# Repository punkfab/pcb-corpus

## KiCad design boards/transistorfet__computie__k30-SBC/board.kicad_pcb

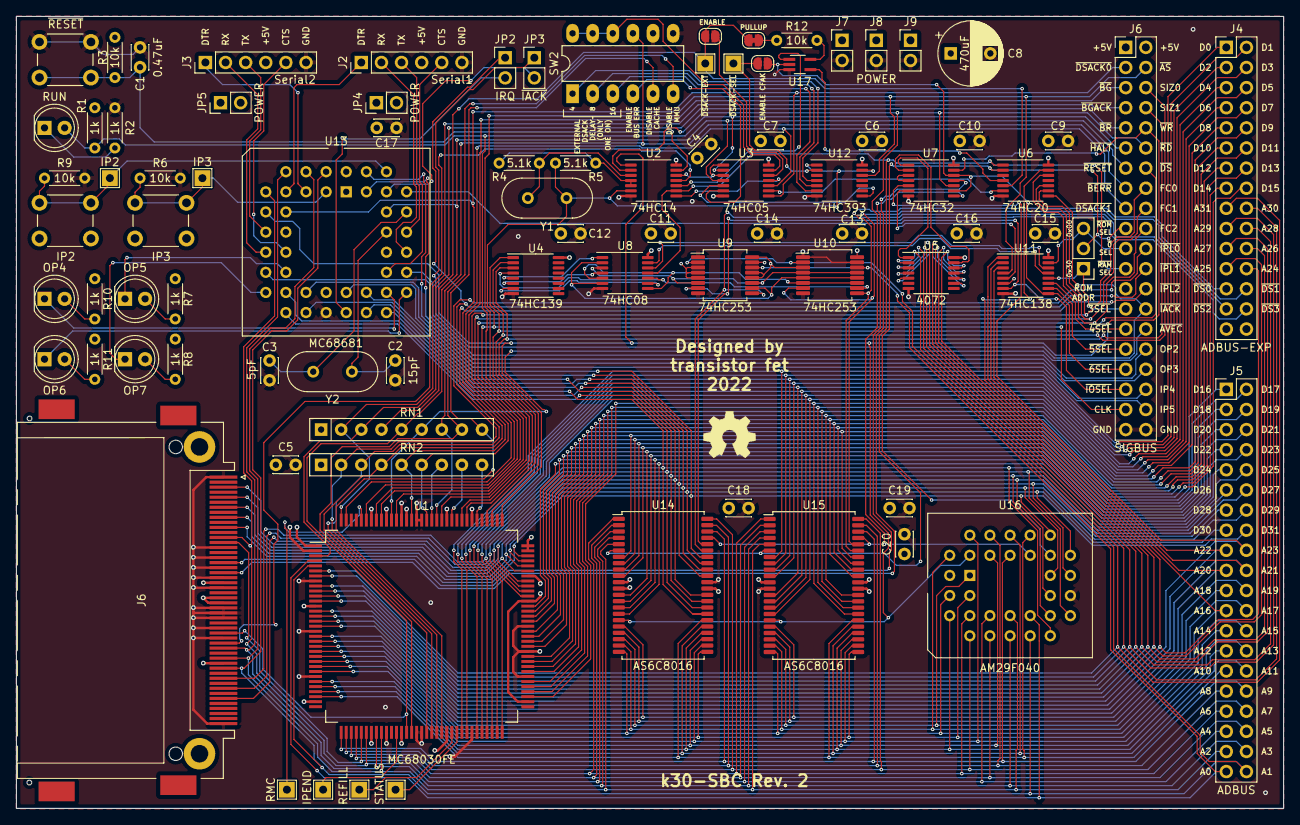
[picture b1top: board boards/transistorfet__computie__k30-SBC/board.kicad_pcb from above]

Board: 4 copper layers, 160.0 x 100.0 mm, 87 parts (0 on the bottom side), 173 nets.

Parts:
C1: 0.47uF; C_Disc_D3.0mm_W2.0mm_P2.50mm
C2: 15pF; C_Disc_D3.0mm_W2.0mm_P2.50mm
C3: 5pF; C_Disc_D3.0mm_W2.0mm_P2.50mm
C4, C5, C6, C7, C9, C10, C11, C12, C13, C14, C15, C16, C17, C18, C19, C20: 0.1uF; C_Disc_D3.0mm_W2.0mm_P2.50mm
C8: 470uF; CP_Radial_D8.0mm_P5.00mm
D1: RUN; LED_D5.0mm
D2: OP5; LED_D5.0mm
D3: OP7; LED_D5.0mm
D4: OP4; LED_D5.0mm
D5: OP6; LED_D5.0mm
J1: CompactFlash; CF-Card_3M_N7E50-Q516RB-40
J2: Serial1; PinHeader_1x06_P2.54mm_Vertical
J3: Serial2; PinHeader_1x06_P2.54mm_Vertical
J4: ADBUS-EXP; PinHeader_2x15_P2.54mm_Vertical
J5: ADBUS; PinHeader_2x20_P2.54mm_Vertical
J6: SIGBUS; PinHeader_2x20_P2.54mm_Vertical
J7, J8, J9: POWER; PinHeader_1x02_P2.54mm_Vertical
JP1: ROMJMP; PinHeader_1x03_P2.54mm_Vertical
JP2: IRQ; PinHeader_1x02_P2.54mm_Vertical
JP3: ~{IACK}; PinHeader_1x02_P2.54mm_Vertical
JP4, JP5: POWER; PinHeader_1x02_P2.54mm_Vertical
JP6: ENABLE; SolderJumper-2_P1.3mm_Open_RoundedPad1.0x1.5mm
JP7: PULLUP; SolderJumper-2_P1.3mm_Bridged_RoundedPad1.0x1.5mm
JP8: ENABLE CFAK; SolderJumper-2_P1.3mm_Open_RoundedPad1.0x1.5mm
R1, R2, R7, R8, R10, R11: 1k; R_Axial_DIN0204_L3.6mm_D1.6mm_P5.08mm_Horizontal
R3, R6, R9, R12: 10k; R_Axial_DIN0204_L3.6mm_D1.6mm_P5.08mm_Horizontal
R4, R5: 5.1k; R_Axial_DIN0204_L3.6mm_D1.6mm_P5.08mm_Horizontal
RN1, RN2: 10k; R_Array_SIP9
SW1: ~{RESET}; SW_PUSH_6mm
SW2: SW_DIP_x06; DIP-12_W7.62mm_LongPads
SW3: IP2; SW_PUSH_6mm
SW4: IP3; SW_PUSH_6mm
TP1: IPEND; TestPoint_THTPad_2.0x2.0mm_Drill1.0mm
TP2: REFILL; TestPoint_THTPad_2.0x2.0mm_Drill1.0mm
TP3: STATUS; TestPoint_THTPad_2.0x2.0mm_Drill1.0mm
TP4: ~{DSACK-EXT}; TestPoint_THTPad_2.0x2.0mm_Drill1.0mm
TP5: IP3; TestPoint_THTPad_2.0x2.0mm_Drill1.0mm
TP6: IP2; TestPoint_THTPad_2.0x2.0mm_Drill1.0mm
TP7: RMC; TestPoint_THTPad_2.0x2.0mm_Drill1.0mm
TP8: ~{DSACK-SEL}; TestPoint_THTPad_2.0x2.0mm_Drill1.0mm
U1: MC68030FE; PQFP-132_24x24mm_P0.635mm
U2: 74HC14; TSSOP-14_4.4x5mm_P0.65mm
U3: 74HC05; TSSOP-14_4.4x5mm_P0.65mm
U4: 74HC139; TSSOP-16_4.4x5mm_P0.65mm
U5: 4072; TSSOP-14_4.4x5mm_P0.65mm
U6: 74HC20; TSSOP-14_4.4x5mm_P0.65mm
U7: 74HC32; TSSOP-14_4.4x5mm_P0.65mm
U8: 74HC08; TSSOP-14_4.4x5mm_P0.65mm
U9, U10: 74HC253; SSOP-16_5.3x6.2mm_P0.65mm
U11: 74HC138; TSSOP-16_4.4x5mm_P0.65mm
U12: 74HC393; TSSOP-14_4.4x5mm_P0.65mm
U13: MC68681; PLCC-44_THT-Socket
U14, U15: AS6C8016; TSOP-II-44_10.16x18.41mm_P0.8mm
U16: AM29F040; PLCC-32_THT-Socket
U17: 74LVC1G32; SOT-353_SC-70-5_Handsoldering
Y1, Y2: Crystal; Crystal_HC49-4H_Vertical

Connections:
+5V: C4.1, C5.1, C6.1, C7.1, C8.1, C9.1, C10.1, C11.1, C12.1, C13.1, C14.1, C15.1, C16.1, C17.1, C18.1, C19.1, C20.1, J1.13, J1.36, J1.38, J1.44, J6.1, J6.2, J7.1, J8.1, J9.1, JP4.1 (A), JP5.1 (A), R1.2, R3.1, R7.2, R8.2, R10.2, R11.2, R12.1, RN1.1 (common), RN2.1 (common), SW3.2, SW4.2, U1.1 (VCC), U1.13 (VCC), U1.32 (VCC), U1.46 (VCC), U1.55 (VCC), U1.68 (VCC), U1.88 (VCC), U1.98 (VCC), U1.99 (VCC), U1.111 (VCC), U1.119 (VCC), U1.123 (VCC), U2.14 (VCC), U3.14 (VCC), U4.16 (VCC), U5.14 (VDD), U6.14 (VCC), U7.14 (VCC), U8.14 (VCC), U9.3 (I3a), U9.4 (I2a), U9.5 (I1a), U9.12 (I2b), U9.13 (I3b), U9.16 (VCC), U10.3 (I3a), U10.16 (VCC), U11.6 (E3), U11.16 (VCC), U12.14 (VCC), U13.44 (VCC), U14.11 (VCC), U14.33 (VCC), U15.11 (VCC), U15.33 (VCC), U16.32 (VCC), U17.5 (VCC)
A0: J5.39, U1.4 (A0), U9.14 (A0), U10.14 (A0), U16.12 (A0)
A1: J1.20, J5.40, U1.5 (A1), U9.2 (A1), U10.2 (A1), U13.2 (RS1), U16.11 (A1)
A2: J1.19, J5.37, U1.42 (A2), U13.4 (RS2), U14.5 (A0), U15.5 (A0), U16.10 (A2)
A3: J1.18, J5.38, U1.41 (A3), U13.6 (RS3), U14.4 (A1), U15.4 (A1), U16.9 (A3)
A4: J1.7, J5.35, U1.39 (A4), U13.7 (RS4), U14.3 (A2), U15.3 (A2), U16.8 (A4)
A5: J1.32, J5.36, U1.38 (A5), U14.2 (A3), U15.2 (A3), U16.7 (A5)
A6: J5.33, U1.37 (A6), U14.1 (A4), U15.1 (A4), U16.6 (A6)
A7: J5.34, U1.36 (A7), U14.44 (A5), U15.44 (A5), U16.5 (A7)
A8: J5.31, U1.35 (A8), U14.43 (A6), U15.43 (A6), U16.27 (A8)
A9: J5.32, U1.34 (A9), U14.42 (A7), U15.42 (A7), U16.26 (A9)
A10: J5.29, U1.31 (A10), U14.28 (A8), U15.28 (A8), U16.23 (A10)
A11: J5.30, U1.30 (A11), U14.27 (A9), U15.27 (A9), U16.25 (A11)
A12: J5.27, U1.29 (A12), U14.26 (A10), U15.26 (A10), U16.4 (A12)
A13: J5.28, U1.28 (A13), U14.25 (A11), U15.25 (A11), U16.28 (A13)
A14: J5.25, U1.26 (A14), U14.24 (A12), U15.24 (A12), U16.29 (A14)
A15: J5.26, U1.25 (A15), U14.23 (A13), U15.23 (A13), U16.3 (A15)
A16: J5.23, U1.24 (A16), U6.13, U14.22 (A14), U15.22 (A14), U16.2 (A16)
A17: J5.24, U1.23 (A17), U14.21 (A15), U15.21 (A15), U16.30 (A17)
A18: J5.21, U1.22 (A18), U14.20 (A16), U15.20 (A16), U16.1 (A18)
A19: J5.22, U1.21 (A19), U14.19 (A17), U15.19 (A17)
A20: J5.19, U1.20 (A20), U11.1 (A0), U14.18 (A18), U15.18 (A18)
A21: J5.20, U1.19 (A21), U11.2 (A1)
A22: J5.17, U1.17 (A22), U11.3 (A2)
A23: J5.18, U1.16 (A23), U7.5
A24: J4.24, U1.15 (A24), U5.12
A25: J4.23, U1.14 (A25), U5.11
A26: J4.22, U1.12 (A26), U5.10
A27: J4.21, U1.11 (A27), U5.9
A28: J4.20, U1.10 (A28), U5.5
A29: J4.19, U1.9 (A29), U5.4
A30: J4.18, U1.7 (A30), U5.3
A31: J4.17, U1.6 (A31), U5.2
ATA-READY: J1.42, U2.11
CLK: J6.37, R5.1, U1.121 (CLK), U2.6, U12.1 (CP), U12.13 (CP), Y1.2
D0: J4.1, U1.58 (D0), U15.7 (Q0)
D1: J4.2, U1.59 (D1), U15.8 (Q1)
D2: J4.3, U1.61 (D2), U15.9 (Q2)
D3: J4.4, U1.62 (D3), U15.10 (Q3)
D4: J4.5, U1.63 (D4), U15.13 (Q4)
D5: J4.6, U1.64 (D5), U15.14 (Q5)
D6: J4.7, U1.65 (D6), U15.15 (Q6)
D7: J4.8, U1.66 (D7), U15.16 (Q7)
D8: J4.9, U1.69 (D8), U15.29 (Q8)
D9: J4.10, U1.70 (D9), U15.30 (Q9)
D10: J4.11, U1.71 (D10), U15.31 (Q10)
D11: J4.12, U1.72 (D11), U15.32 (Q11)
D12: J4.13, U1.74 (D12), U15.35 (Q12)
D13: J4.14, U1.75 (D13), U15.36 (Q13)
D14: J4.15, U1.76 (D14), U15.37 (Q14)
D15: J4.16, U1.77 (D15), U15.38 (Q15)
D16: J5.1, U1.79 (D16), U14.7 (Q0)
D17: J5.2, U1.80 (D17), U14.8 (Q1)
D18: J5.3, U1.81 (D18), U14.9 (Q2)
D19: J5.4, U1.82 (D19), U14.10 (Q3)
D20: J5.5, U1.84 (D20), U14.13 (Q4)
D21: J5.6, U1.85 (D21), U14.14 (Q5)
D22: J5.7, U1.86 (D22), U14.15 (Q6)
D23: J5.8, U1.87 (D23), U14.16 (Q7)
D24: J1.21, J5.9, U1.89 (D24), U13.28 (D0), U14.29 (Q8), U16.13 (Q0)
D25: J1.22, J5.10, U1.90 (D25), U13.18 (D1), U14.30 (Q9), U16.14 (Q1)
D26: J1.23, J5.11, U1.91 (D26), U13.27 (D2), U14.31 (Q10), U16.15 (Q2)
D27: J1.2, J5.12, U1.92 (D27), U13.19 (D3), U14.32 (Q11), U16.17 (Q3)
D28: J1.3, J5.13, U1.94 (D28), U13.26 (D4), U14.35 (Q12), U16.18 (Q4)
D29: J1.4, J5.14, U1.95 (D29), U13.20 (D5), U14.36 (Q13), U16.19 (Q5)
D30: J1.5, J5.15, U1.96 (D30), U13.25 (D6), U14.37 (Q14), U16.20 (Q6)
D31: J1.6, J5.16, U1.97 (D31), U13.21 (D7), U14.38 (Q15), U16.21 (Q7)
FC0: J6.16, U1.127 (FC0), U6.9
FC1: J6.18, U1.125 (FC1), U6.10
FC2: J6.20, U1.124 (FC2), U6.12
GND: C1.2, C2.1, C3.1, C4.2, C5.2, C6.2, C7.2, C8.2, C9.2, C10.2, C11.2, C12.2, C13.2, C14.2, C15.2, C16.2, C17.2, C18.2, C19.2, C20.2, J1.1, J1.8, J1.9, J1.10, J1.11, J1.12, J1.14, J1.15, J1.16, J1.17, J1.39, J1.50, J2.6, J3.6, J6.39, J6.40, J7.2, J8.2, J9.2, R2.1, R6.2, R9.2, SW1.1, SW2.7, SW2.8, U1.2 (GND), U1.8 (GND), U1.18 (GND), U1.27 (GND), U1.40 (GND), U1.43 (GND), U1.49 (GND), U1.50 (GND), U1.60 (GND), U1.73 (GND), U1.78 (GND), U1.83 (GND), U1.93 (GND), U1.106 (GND), U1.116 (GND), U1.117 (GND), U1.120 (GND), U1.126 (GND), U2.7 (GND), U3.7 (GND), U4.8 (GND), U5.7 (VSS), U6.7 (GND), U7.7 (GND), U8.7 (GND), U9.1 (OEa), U9.8 (GND), U9.15 (OEb), U10.1 (OEa), U10.8 (GND), U10.15 (OEb), U11.8 (GND), U12.7 (GND), U13.22 (GND), U14.12 (VSS), U14.34 (VSS), U15.12 (VSS), U15.34 (VSS), U16.16 (GND), U17.3 (GND)
IP4: J6.36, U13.43 (IP4)
IP5: J6.38, U13.42 (IP5)
unnamed: C1.1, R3.2, SW1.2, U2.13
unnamed: C2.2, U13.36 (X1/CLK), Y2.2
unnamed: C3.2, U13.37 (X2), Y2.1
unnamed: D1.1 (K), R2.2
unnamed: D2.1 (K), U13.16 (OP5)
unnamed: D2.2 (A), R7.1
unnamed: D3.1 (K), U13.17 (OP7)
unnamed: D3.2 (A), R8.1
unnamed: D4.1 (K), U13.30 (OP4)
unnamed: D4.2 (A), R10.1
unnamed: D5.1 (K), U13.29 (OP6)
unnamed: D5.2 (A), R11.1
unnamed: J2.1, U13.8 (IP0)
unnamed: J2.2, U13.33 (TXDA)
unnamed: J2.3, U13.35 (RXDA)
unnamed: J2.4, JP4.2 (B)
unnamed: J2.5, U13.32 (OP0)
unnamed: J3.1, U13.5 (IP1)
unnamed: J3.2, U13.13 (TXDB)
unnamed: J3.3, U13.11 (RXDB)
unnamed: J3.4, JP5.2 (B)
unnamed: J3.5, U13.14 (OP1)
unnamed: JP6.1 (A), U3.12
unnamed: JP7.2 (B), R12.2
unnamed: R4.1, R5.2, U2.4, U2.5
unnamed: R4.2, U2.3, Y1.1
unnamed: R6.1, SW4.1, TP5.1, U13.3 (IP3)
unnamed: R9.1, SW3.1, TP6.1, U13.40 (IP2)
unnamed: RN2.7 (R6), U1.114 (STERM)
unnamed: RN2.8 (R7), U1.110 (CBACK)
unnamed: RN2.9 (R8), U1.105 (CIIN)
unnamed: SW2.1, U12.4 (Q1)
unnamed: SW2.2, U12.5 (Q2)
unnamed: SW2.3, U12.6 (Q3)
unnamed: SW2.4, U3.6
unnamed: SW2.10, SW2.11, SW2.12, U3.13
unnamed: TP1.1, U1.45 (IPEND)
unnamed: TP2.1, U1.56 (REFILL)
unnamed: TP3.1, U1.57 (STATUS)
unnamed: TP7.1, U1.128 (RMC)
unnamed: JP8.2 (B), TP8.1, U12.2 (MR)
unnamed: U2.8, U3.11
unnamed: U2.12, U3.1, U3.3
unnamed: U3.9, U6.6
unnamed: U4.5 (O1), U8.1
unnamed: U4.6 (O2), U8.4
unnamed: U4.7 (O3), U8.9
unnamed: U5.1, U7.1
unnamed: U5.13, U7.2
unnamed: U7.3, U7.4
unnamed: U4.4 (O0), U8.10, U10.10 (I0b)
unnamed: U8.5, U8.8, U10.6 (I0a), U10.11 (I1b)
unnamed: U8.2, U8.6, U9.10 (I0b), U10.5 (I1a), U10.12 (I2b)
unnamed: U8.3, U9.6 (I0a), U9.11 (I1b), U10.4 (I2a), U10.13 (I3b)
unnamed: U7.6, U11.5 (E2)
unnamed: U8.13, U11.13 (O2)
unnamed: U8.12, U11.14 (O1)
unnamed: U3.5, U12.8 (Q3)
unnamed: U2.10, U17.1
OP2: J6.32, U13.31 (OP2)
OP3: J6.34, U13.15 (OP3)
SIZ0: J6.6, U1.103 (SIZ0), U4.2 (A0)
SIZ1: J6.8, U1.102 (SIZ1), U4.3 (A1)
~0SEL: J6.21, JP1.3 (B), U11.15 (O0)
~3SEL: J6.27, JP1.1 (A), U11.12 (O3)
~4SEL: J6.29, U11.11 (O4)
~5SEL: J6.31, U11.10 (O5)
~6SEL: J6.33, JP8.1 (A), U7.9, U7.12, U11.9 (O6), U17.2
~AS: J6.4, U1.108 (AS), U11.4 (E1), U12.12 (MR)
~ATA-DSACK: U6.4, U17.4
~AVEC: J6.30, RN1.6 (R5), U1.122 (AVEC)
~BERR: J6.15, RN1.7 (R6), SW2.9, U1.113 (BERR)
~BGACK: J6.7, RN1.2 (R1), U1.132 (BGACK)
~BG: J6.5, U1.131 (BG)
~BR: J6.9, RN1.3 (R2), U1.3 (BR)
~CDIS: RN1.9 (R8), SW2.5, U1.54 (CDIS)
~DS0: J4.25, U10.9 (Zb), U15.39 (~LB)
~DS1: J4.26, U10.7 (Za), U15.40 (~UB)
~DS2: J4.27, U9.9 (Zb), U14.39 (~LB)
~DS3: J4.28, U9.7 (Za), U14.40 (~UB)
~DSACK0: J6.3, RN2.5 (R4), U1.118 (DSACK0), U3.8, U13.10 (DTACK)
~DSACK1: J6.17, RN2.6 (R5), U1.115 (DSACK1), U3.10
~DSACK-EXT: JP6.2 (B), JP7.1 (A), RN1.4 (R3), TP4.1, U6.5
~DS: J6.14, U1.107 (DS), U4.1 (E)
~HALT: D1.2 (A), J6.11, R1.1, U1.112 (HALT), U3.2
~IACK: J6.28, JP3.1 (A), U6.8
~IORD: J1.34, U7.8
~IOSEL: J6.35, U11.7 (O7), U13.39 (CS)
~IOWR: J1.35, U7.11
~IPL0: J6.22, RN2.2 (R1), U1.53 (IPL0)
~IPL1: J6.24, JP2.1 (A), RN2.3 (R2), U1.52 (IPL1)
~IPL2: J6.26, RN2.4 (R3), U1.51 (IPL2)
~MMUDIS: RN1.8 (R7), SW2.6, U1.48 (MMUDIS)
~RAMSEL: J6.23, U2.9, U6.1, U8.11, U14.6 (~CE), U15.6 (~CE)
~RD: J6.12, U2.2, U7.10, U14.41 (~OE), U15.41 (~OE), U16.24 (~OE)
~RESET: J1.41, J6.13, RN1.5 (R4), U1.47 (RESET), U3.4, U13.38 (RESET)
~ROMSEL: J6.19, JP1.2 (C), U6.2, U16.22 (~CS)
~SIACK: JP3.2 (B), U13.41 (IACK)
~SIRQ: JP2.2 (B), U13.24 (IRQ)
~WR: J6.10, U1.100 (R/W), U2.1, U7.13, U13.9 (R/W), U14.17 (~WE), U15.17 (~WE), U16.31 (~WE)

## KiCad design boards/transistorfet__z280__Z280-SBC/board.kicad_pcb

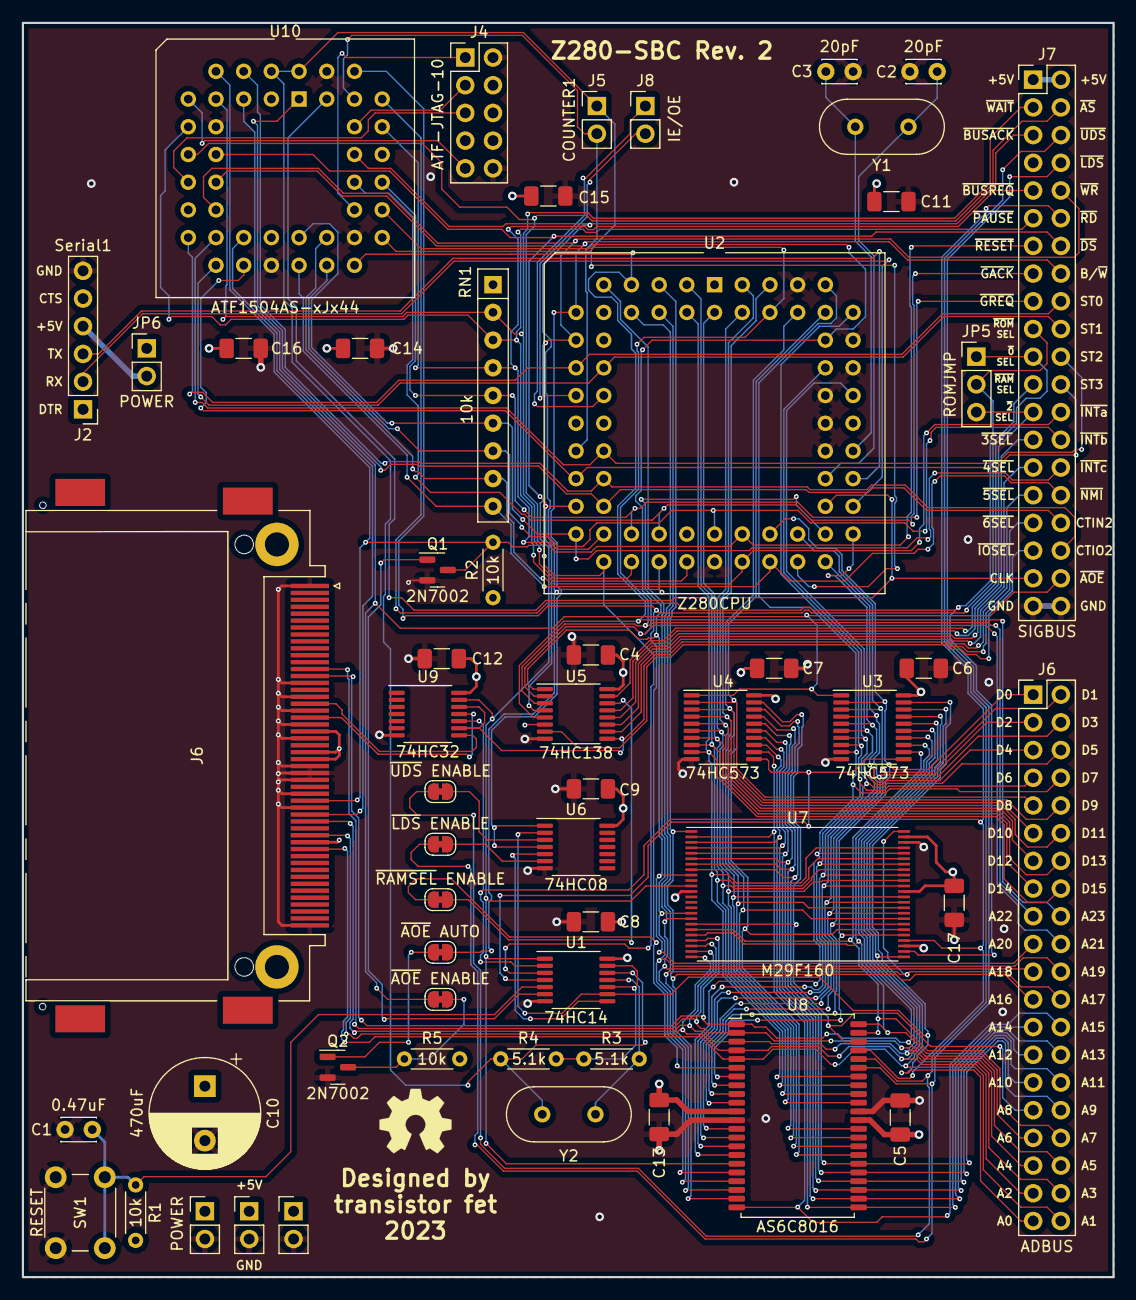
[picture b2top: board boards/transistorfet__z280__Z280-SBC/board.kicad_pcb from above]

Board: 4 copper layers, 100.0 x 115.0 mm, 55 parts (0 on the bottom side), 104 nets.

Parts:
C1: 0.47uF; C_Disc_D3.0mm_W2.0mm_P2.50mm
C2, C3: 20pF; C_Disc_D3.0mm_W2.0mm_P2.50mm
C4, C5, C6, C7, C8, C9, C11, C12, C13, C14, C15, C16, C17: 0.1uF; C_1206_3216Metric_Pad1.33x1.80mm_HandSolder
C10: 470uF; CP_Radial_D10.0mm_P5.00mm
J1: CompactFlash; CF-Card_3M_N7E50-Q516RB-40
J2: Serial1; PinHeader_1x06_P2.54mm_Vertical
J3, J9, J10: POWER; PinHeader_1x02_P2.54mm_Vertical
J4: ATF-JTAG-10; PinHeader_2x05_P2.54mm_Vertical
J5: COUNTER1; PinHeader_1x02_P2.54mm_Vertical
J6: ADBUS; PinHeader_2x20_P2.54mm_Vertical
J7: SIGBUS; PinHeader_2x20_P2.54mm_Vertical
J8: IE/OE; PinHeader_1x02_P2.54mm_Vertical
JP1: ~{AOE} ENABLE; SolderJumper-2_P1.3mm_Bridged_RoundedPad1.0x1.5mm
JP2: ~{UDS} ENABLE; SolderJumper-2_P1.3mm_Bridged_RoundedPad1.0x1.5mm
JP3: ~{LDS} ENABLE; SolderJumper-2_P1.3mm_Bridged_RoundedPad1.0x1.5mm
JP4: ~{RAMSEL} ENABLE; SolderJumper-2_P1.3mm_Bridged_RoundedPad1.0x1.5mm
JP5: ROMJMP; PinHeader_1x03_P2.54mm_Vertical
JP6: POWER; PinHeader_1x02_P2.54mm_Vertical
JP7: ~{AOE} AUTO; SolderJumper-2_P1.3mm_Bridged_RoundedPad1.0x1.5mm
Q1, Q2: 2N7002; SOT-23
R1, R2, R5: 10k; R_Axial_DIN0204_L3.6mm_D1.6mm_P5.08mm_Horizontal
R3, R4: 5.1k; R_Axial_DIN0204_L3.6mm_D1.6mm_P5.08mm_Horizontal
RN1: 10k; R_Array_SIP9
SW1: RESET; SW_PUSH_6mm
U1: 74HC14; TSSOP-14_4.4x5mm_P0.65mm
U2: Z280CPU; PLCC-68_THT-Socket
U3, U4: 74HC573; TSSOP-20_4.4x6.5mm_P0.65mm
U5: 74HC138; TSSOP-16_4.4x5mm_P0.65mm
U6: 74HC08; TSSOP-14_4.4x5mm_P0.65mm
U7: M29F160; TSOP-I-48_18.4x12mm_P0.5mm
U8: AS6C8016; TSOP-II-44_10.16x18.41mm_P0.8mm
U9: 74HC32; TSSOP-14_4.4x5mm_P0.65mm
U10: ATF1504AS-xJx44; PLCC-44_THT-Socket
Y1, Y2: Crystal; Crystal_HC49-4H_Vertical

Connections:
+5V: C4.1, C5.1, C6.1, C7.1, C8.1, C9.1, C10.1, C11.1, C12.1, C13.1, C14.1, C15.1, C16.1, C17.1, J1.13, J1.36, J1.38, J1.44, J3.1, J4.7 (VCC), J7.1, J7.2, J9.1, J10.1, JP6.1 (A), R1.1, R2.1, R5.1, RN1.1 (common), U1.14 (VCC), U2.18 (VCC), U2.19 (VCC), U3.20 (VCC), U4.20 (VCC), U5.6 (E3), U5.16 (VCC), U6.14 (VCC), U7.12 (~RST), U7.37 (VCC), U7.47 (~BYTE), U8.11 (VCC), U8.33 (VCC), U9.14 (VCC), U10.3 (VCC), U10.15 (VCC), U10.23 (VCC), U10.35 (VCC)
A0: J6.39, U1.9, U3.19 (Q0), U6.2
A1: J1.20, J6.40, U3.18 (Q1), U7.25 (A0), U8.5 (A0)
A2: J1.19, J6.37, U3.17 (Q2), U7.24 (A1), U8.4 (A1)
A3: J1.18, J6.38, U3.16 (Q3), U7.23 (A2), U8.3 (A2)
A4: J1.7, J6.35, U3.15 (Q4), U7.22 (A3), U8.2 (A3)
A5: J1.32, J6.36, U3.14 (Q5), U7.21 (A4), U8.1 (A4)
A6: J6.33, U3.13 (Q6), U7.20 (A5), U8.44 (A5)
A7: J6.34, U3.12 (Q7), U7.19 (A6), U8.43 (A6)
A8: J6.31, U4.19 (Q0), U7.18 (A7), U8.42 (A7)
A9: J6.32, U4.18 (Q1), U7.8 (A8), U8.28 (A8)
A10: J6.29, U4.17 (Q2), U7.7 (A9), U8.27 (A9)
A11: J6.30, U4.16 (Q3), U7.6 (A10), U8.26 (A10)
A12: J6.27, U4.15 (Q4), U7.5 (A11), U8.25 (A11)
A13: J6.28, U4.14 (Q5), U7.4 (A12), U8.24 (A12)
A14: J6.25, U4.13 (Q6), U7.3 (A13), U8.23 (A13)
A15: J6.26, U4.12 (Q7), U7.2 (A14), U8.22 (A14)
A16: J6.23, U2.5 (A16), U7.1 (A15), U8.21 (A15)
A17: J6.24, U2.6 (A17), U7.48 (A16), U8.20 (A16)
A18: J6.21, U2.8 (A18), U7.17 (A17), U8.19 (A17)
A19: J6.22, U2.9 (A19), U7.16 (A18), U8.18 (A18)
A20: J6.19, U2.45 (A20), U5.1 (A0), U7.9 (A19)
A21: J6.20, U2.59 (A21), U5.2 (A1), U10.31 (I/O)
A22: J6.17, U2.66 (A22), U5.3 (A2), U10.29 (I/O)
A23: J6.18, U2.7 (A23), U5.5 (E2), U10.28 (I/O)
ALE: U1.4, U3.11 (Load), U4.11 (Load)
ATA-READY: J1.42, U10.21 (I/O)
B/~W: J7.16, U2.10 (B/~W), U6.1, U6.4, U10.14 (I/O)
CLK: J7.37, U2.47 (CLK), U10.43 (I/GCLK1)
CTIN1: J5.1, R4.1, U1.12, U2.41 (CTIN1), U10.2 (I/OE2/GCLK2), U10.44 (I/OE1), Y2.2
CTIN2: J7.34, U2.25 (CTIN2), U10.1 (I/GCLR)
CTIO1: J5.2, U2.20 (CTIO1), U10.41 (I/O/GCLK3)
CTIO2: J7.36, U2.23 (CTIO2), U10.4 (I/O)
D0: J6.1, U2.40 (AD0), U3.2 (D0), U7.29 (Q0), U8.7 (Q0)
D1: J6.2, U2.42 (AD1), U3.3 (D1), U7.31 (Q1), U8.8 (Q1)
D2: J6.3, U2.43 (AD2), U3.4 (D2), U7.33 (Q2), U8.9 (Q2)
D3: J6.4, U2.44 (AD3), U3.5 (D3), U7.35 (Q3), U8.10 (Q3)
D4: J6.5, U2.54 (AD4), U3.6 (D4), U7.38 (Q4), U8.13 (Q4)
D5: J6.6, U2.57 (AD5), U3.7 (D5), U7.40 (Q5), U8.14 (Q5)
D6: J6.7, U2.60 (AD6), U3.8 (D6), U7.42 (Q6), U8.15 (Q6)
D7: J6.8, U2.61 (AD7), U3.9 (D7), U7.44 (Q7), U8.16 (Q7)
D8: J6.9, U2.62 (AD8), U4.2 (D0), U7.30 (Q8), U8.29 (Q8)
D9: J6.10, U2.64 (AD9), U4.3 (D1), U7.32 (Q9), U8.30 (Q9)
D10: J6.11, U2.65 (AD10), U4.4 (D2), U7.34 (Q10), U8.31 (Q10)
D11: J6.12, U2.67 (AD11), U4.5 (D3), U7.36 (Q11), U8.32 (Q11)
D12: J6.13, U2.68 (AD12), U4.6 (D4), U7.39 (Q12), U8.35 (Q12)
D13: J6.14, U2.2 (AD13), U4.7 (D5), U7.41 (Q13), U8.36 (Q13)
D14: J6.15, U2.3 (AD14), U4.8 (D6), U7.43 (Q14), U8.37 (Q14)
D15: J6.16, U2.4 (AD15), U4.9 (D7), U7.45 (Q15), U8.38 (Q15)
GND: C1.2, C2.1, C3.1, C4.2, C5.2, C6.2, C7.2, C8.2, C9.2, C10.2, C11.2, C12.2, C13.2, C14.2, C15.2, C16.2, C17.2, J1.1, J1.8, J1.9, J1.10, J1.11, J1.12, J1.14, J1.15, J1.16, J1.17, J1.39, J1.50, J2.6, J3.2, J4.2 (GND), J4.10 (GND), J7.39, J7.40, J9.2, J10.2, Q1.2 (S), Q2.2 (S), SW1.1, U1.7 (GND), U2.1 (GND), U2.35 (GND), U2.51 (GND), U2.53 (GND), U2.55 (~RDY0), U2.56 (~RDY1), U2.58 (~RDY3), U2.63 (~RDY2), U3.10 (GND), U4.10 (GND), U5.8 (GND), U6.7 (GND), U7.27 (GND), U7.46 (GND), U8.12 (VSS), U8.34 (VSS), U9.7 (GND), U10.10 (GND), U10.22 (GND), U10.30 (GND), U10.42 (GND)
unnamed: C1.1, R1.2, SW1.2, U1.5
unnamed: C2.2, U2.49 (XTALO), Y1.1
unnamed: C3.2, U2.50 (XTALI), Y1.2
unnamed: J2.4, JP6.2 (B)
unnamed: J4.1 (TCK), U10.32 (I/O/TCK)
unnamed: J4.3 (TDO), U10.38 (I/O/TDO)
unnamed: J4.5 (TMS), U10.13 (I/O/TMS)
unnamed: J4.9 (TDI), U10.7 (I/O/TDI)
unnamed: JP1.2 (B), Q2.3 (D), R5.2
unnamed: JP2.1 (A), U6.3
unnamed: JP3.1 (A), U6.6
unnamed: JP4.1 (A), U5.14 (O1)
unnamed: JP7.1 (A), Q2.1 (G)
unnamed: Q1.1 (G), U1.6
unnamed: R3.1, R4.2, U1.10, U1.13
unnamed: R3.2, U1.11, Y2.1
unnamed: U1.8, U6.5
RxD: J2.3, U2.48 (RxD)
R/~W: J7.10, U1.1, U2.12 (R/~W), U7.11 (~WE), U8.17 (~WE), U9.13, U10.16 (I/O)
ST0: J7.18, U2.14 (ST0), U10.17 (I/O)
ST1: J7.20, U2.15 (ST1), U10.18 (I/O)
ST2: J7.22, U2.21 (ST2), U10.19 (I/O)
ST3: J7.24, U2.22 (ST3), U10.20 (I/O)
TxD: J2.2, U2.46 (TxD)
~0SEL: J7.21, JP5.1 (A), U5.15 (O0)
~2SEL: J7.25, JP5.3 (B), U5.13 (O2)
~3SEL: J7.27, U5.12 (O3)
~4SEL: J7.29, U5.11 (O4)
~5SEL: J7.31, U5.10 (O5)
~6SEL: J7.33, U5.9 (O6), U9.9, U9.12
~AOE: J7.38, JP1.1 (A), U3.1 (OE), U4.1 (OE), U10.5 (I/O)
~AS: J7.4, U1.3, U2.27 (~AS), U10.11 (I/O/PD1)
~BUSACK: J7.5, JP7.2 (B), U2.31 (~BUSACK), U10.36 (I/O)
~BUSREQ: J7.9, RN1.4 (R3), U2.28 (~BUSREQ), U10.37 (I/O)
~DS: J7.14, U2.24 (~DS), U5.4 (E1), U10.12 (I/O)
~GACK: J7.15, U2.32 (CTIN0/~GACK), U10.34 (I/O)
~GREQ: J7.17, RN1.5 (R4), U2.30 (CTIO0/~GREQ), U10.33 (I/O)
~IE: J8.1, U2.17 (~IE)
~INTa: J7.26, RN1.8 (R7), U2.37 (~INTa/EOPa), U10.27 (I/O)
~INTb: J7.28, RN1.7 (R6), U2.36 (~INTb/EOPb), U10.26 (I/O)
~INTc: J7.30, RN1.6 (R5), U2.26 (~INTc), U10.25 (I/O/PD2)
~IORD: J1.34, U9.8
~IOSEL: J7.35, U5.7 (O7)
~IOWR: J1.35, U9.11
~LDS: J7.8, JP3.2 (B), U8.39 (~LB)
~NMI: J7.32, RN1.9 (R8), U2.39 (~NMI), U10.24 (I/O)
~OE: J8.2, U2.16 (~OE)
~PAUSE: J7.11, RN1.3 (R2), U2.33 (~PAUSE), U10.9 (I/O)
~RAMSEL: J7.23, JP4.2 (B), U8.6 (~CE), U10.40 (I/O)
~RD: J7.12, U1.2, U7.28 (~OE), U8.41 (~OE), U9.10
~RESET: J1.41, J7.13, Q1.3 (D), R2.2, U2.38 (~RESET), U10.6 (I/O)
~ROMSEL: J7.19, JP5.2 (C), U7.26 (~CS), U10.39 (I/O)
~UDS: J7.6, JP2.2 (B), U8.40 (~UB)
~WAIT: J7.3, RN1.2 (R1), U2.29 (~WAIT), U10.8 (I/O)

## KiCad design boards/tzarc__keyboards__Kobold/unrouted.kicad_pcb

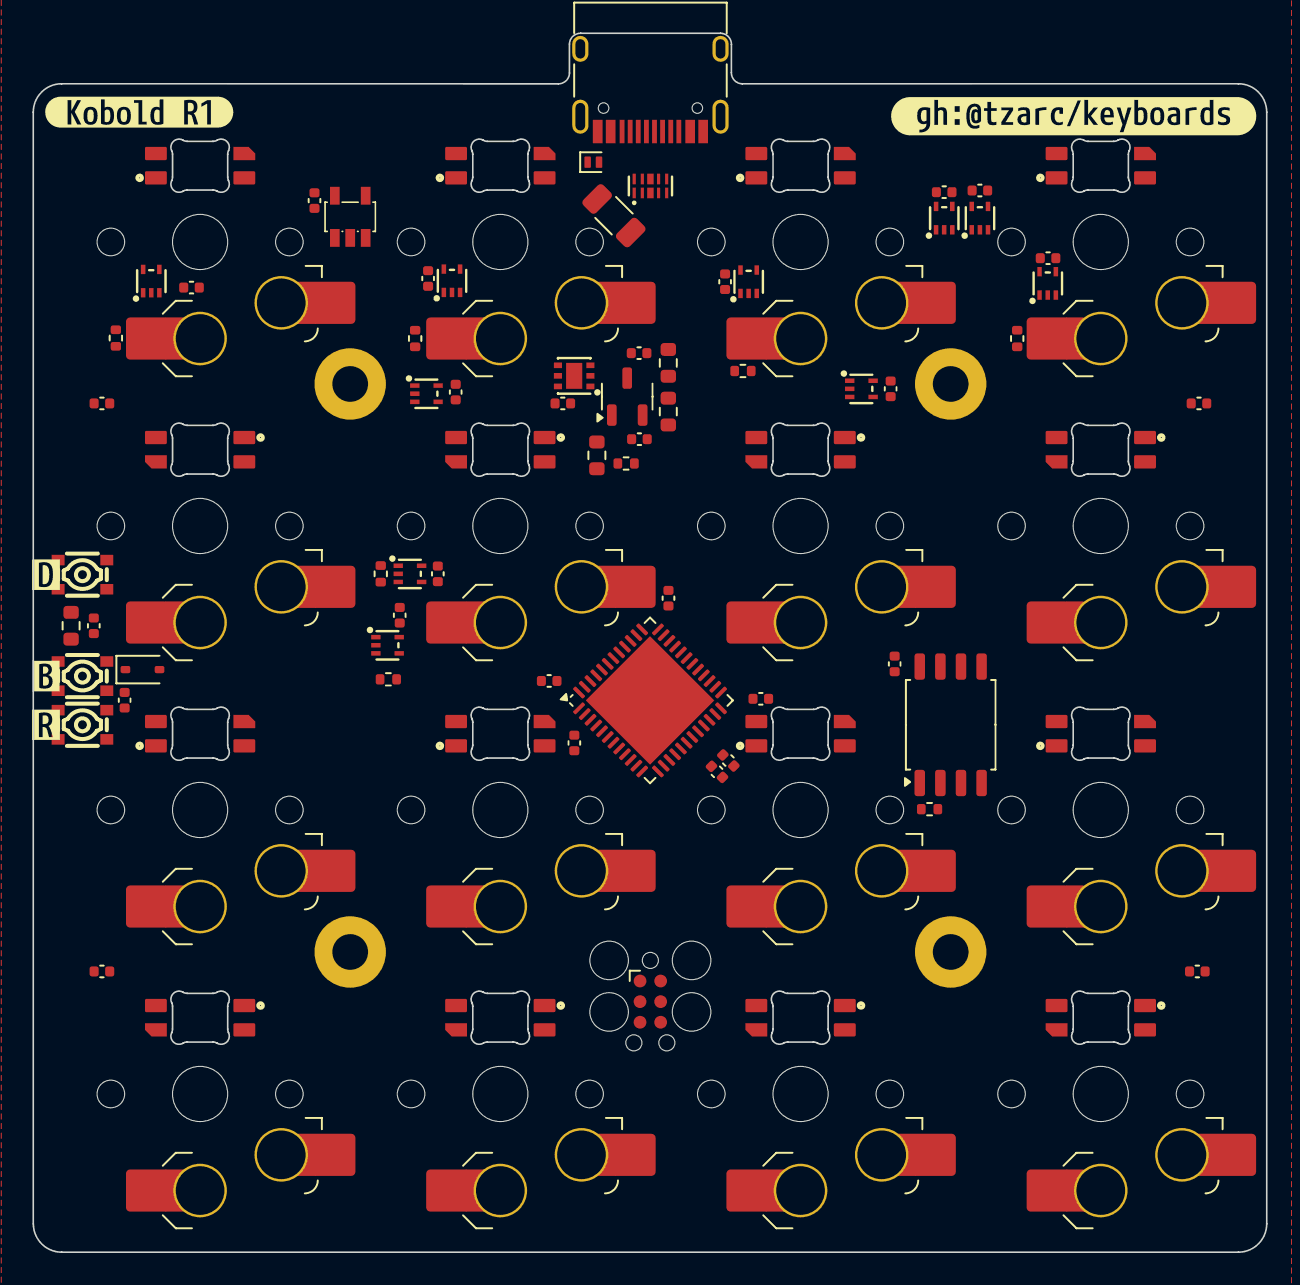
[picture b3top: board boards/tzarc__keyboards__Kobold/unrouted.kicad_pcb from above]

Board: 4 copper layers, 76.0 x 75.1 mm, 104 parts (0 on the bottom side), 66 nets, no tracks yet.

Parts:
C1, C2, C3, C10, C11, C12, C13, C14, C15, C16, C17, C18, C19, C20, C21, C22, C23, C24, C25, C26, C27: 100n; C_0402_1005Metric
C4, C5, C6, C7, C8, C9: 4.7u; C_0402_1005Metric
D1, D2, D3, D4, D9, D10, D11, D12: RGB; LED_choc_6028R
D5, D6, D7, D8, D13, D14, D15, D16: RGB; LED_choc_6028R-ROT
D17: H5VL10B; D_SOD-882
D18: 1N4148; D_SOD-323
H1, H2, H3, H4: 2mm; MountingHole_2.2mm_M2_Pad
J1: TYPE-C-31-M-12; USB_C_Receptacle_HRO_TYPE-C-31-M-12
J2: TC2030; Tag-Connect_TC2030-IDC-FP_2x03_P1.27mm_Vertical
R1, R6, R7, R8, R11, R12: 10k; R_0402_1005Metric
R2, R4, R5, R9: 75k; R_0603_1608Metric
R3: 0.05R; R_1206_3216Metric
R10, R13: 1k; R_0402_1005Metric
SW1, SW2, SW3, SW4, SW5, SW6, SW7, SW8, SW9, SW10, SW11, SW12, SW13, SW14, SW15, SW16: Push; SW_choc_v1_HS_CPG135001S30_1u
SW17: BOOT0; SW-SMD_4P-L3.0-W2.6-P1.80-LS3.4-TL
SW18: DFU; SW-SMD_4P-L3.0-W2.6-P1.80-LS3.4-TL
SW19: nRST; SW-SMD_4P-L3.0-W2.6-P1.80-LS3.4-TL
U1, U2, U9, U11, U13, U15, U16: SN74LVC1G14DRL; SOT-553-5_L1.6-W1.2-P0.50-LS1.6-BL
U3: AP2552FDC-7; WDFN-6_L2.0-W2.0-P0.65-BL-EP-1
U4: XC6206PxxxMR; SOT-23-3
U5: INA180A4; SOT-23-5_L3.0-W1.7-P0.95-LS2.8-BR
U6: H5VU25U; DFN2510-10_L2.5-W1.0-P0.50-BL
U7: STM32G431CBU6; QFN-48-1EP_7x7mm_P0.5mm_EP5.6x5.6mm
U8: W25Q128JVSIQ; SOIC-8_5.3x5.3mm_P1.27mm
U10, U12, U14: SN74AHC1G08DRL; SOT-553-5_L1.6-W1.2-P0.50-LS1.6-BL
kibuzzard-677E65CD: G***; kibuzzard-677E65CD
kibuzzard-677E65D8: G***; kibuzzard-677E65D8
kibuzzard-677E65DF: G***; kibuzzard-677E65DF
kibuzzard-677E6627: G***; kibuzzard-677E6627
kibuzzard-677E6634: G***; kibuzzard-677E6634

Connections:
+3.3V: C9.1, C11.1, C12.1, C13.1, C14.1, C15.1, C16.1, C17.1, C18.1, C20.1, C21.1, C22.1, C23.1, C24.1, C25.1, C26.1, J2.1 (VCC), R1.2, R6.2, R7.2, R8.2, R11.2, R12.2, SW17.1, SW17.2, SW18.1, SW18.2, U4.2 (VO), U7.1 (VBAT), U7.20 (VREF+), U7.21 (VDDA), U7.23 (VDD), U7.35 (VDD), U7.48 (VDD), U8.8 (VCC), U9.5 (VCC), U10.5 (VCC), U11.5 (VCC), U12.5 (VCC), U13.5 (VCC), U14.5 (VCC), U15.5 (VCC), U16.5 (VCC)
/VBUS_IN: D17.2 (A2), J1.A4 (VBUS), J1.A9 (VBUS), J1.B4 (VBUS), J1.B9 (VBUS), R3.1, U5.3 (+)
ADC1_IN12: R4.2, R5.1, U7.18 (PB1)
ADC2_IN12: U5.1, U7.19 (PB2)
BOOT0: C19.1, D18.1 (K), R9.1, SW17.3, SW17.4, U7.46 (PB8)
CC1: J1.A5 (CC1), U6.5, U6.6, U7.31 (PA9), U7.44 (PB6)
CC2: J1.B5 (CC2), U6.1, U6.10, U7.32 (PA10), U7.42 (PB4)
D+: J1.A6 (D+), J1.B6 (D+), U6.2, U6.9, U7.34 (PA12)
D-: J1.A7 (D-), J1.B7 (D-), U6.4, U6.7, U7.33 (PA11)
FLASH_CS: R6.1, U7.22 (PB10), U8.1 (~CS)
GND: C1.2, C2.2, C3.1, C4.2, C5.2, C6.2, C7.2, C8.2, C9.2, C10.2, C11.2, C12.2, C13.2, C14.2, C15.2, C16.2, C17.2, C18.2, C19.2, C20.2, C21.2, C22.2, C23.2, C24.2, C25.2, C26.2, C27.2, D1.3 (VSS), D2.3 (VSS), D3.3 (VSS), D4.3 (VSS), D5.3 (VSS), D6.3 (VSS), D7.3 (VSS), D8.3 (VSS), D9.3 (VSS), D10.3 (VSS), D11.3 (VSS), D12.3 (VSS), D13.3 (VSS), D14.3 (VSS), D15.3 (VSS), D16.3 (VSS), D17.1 (A1), H1.1, H2.1, H3.1, H4.1, J1.A1 (GND), J1.A12 (GND), J1.B1 (GND), J1.B12 (GND), J1.S1 (SHIELD), J2.5 (GND), R2.1, R5.2, R9.2, SW1.1, SW2.1, SW3.1, SW4.1, SW5.1, SW6.1, SW7.1, SW8.1, SW9.1, SW10.1, SW11.1, SW12.1, SW13.1, SW14.1, SW15.1, SW16.1, SW19.3, SW19.4, U1.3 (GND), U2.3 (GND), U3.5 (GND), U3.7 (EP), U4.1 (GND), U5.2 (GND), U6.3, U6.8, U7.49 (VSS), U8.4 (GND), U9.3 (GND), U10.3 (GND), U11.3 (GND), U12.3 (GND), U13.3 (GND), U14.3 (GND), U15.3 (GND), U16.3 (GND)
unnamed: D1.2 (DOUT), D2.4 (DIN)
unnamed: D2.2 (DOUT), D3.4 (DIN)
unnamed: D3.2 (DOUT), D4.4 (DIN)
unnamed: D4.2 (DOUT), D8.4 (DIN)
unnamed: D5.4 (DIN), D6.2 (DOUT)
unnamed: D5.2 (DOUT), D9.4 (DIN)
unnamed: D6.4 (DIN), D7.2 (DOUT)
unnamed: D7.4 (DIN), D8.2 (DOUT)
unnamed: D9.2 (DOUT), D10.4 (DIN)
unnamed: D10.2 (DOUT), D11.4 (DIN)
unnamed: D11.2 (DOUT), D12.4 (DIN)
unnamed: D12.2 (DOUT), D16.4 (DIN)
unnamed: D13.4 (DIN), D14.2 (DOUT)
unnamed: D14.4 (DIN), D15.2 (DOUT)
unnamed: D15.4 (DIN), D16.2 (DOUT)
unnamed: D18.2 (A), R10.1, SW18.3, SW18.4, U15.2
unnamed: R10.2, U12.4
unnamed: R13.2, U15.4
unnamed: U1.4, U2.2
unnamed: R2.2, U3.2 (ILIM)
unnamed: U9.4, U10.1
unnamed: U10.2, U11.4
unnamed: U10.4, U12.1
unnamed: U12.2, U14.4
unnamed: U13.4, U14.1
unnamed: U14.2, U16.4
RGB_PWM_3V3: U1.2, U7.43 (PB5)
RGB_PWM_5V: D1.4 (DIN), U2.4
RGB_PWR: C1.1, C2.1, C4.1, C5.1, C6.1, C7.1, D1.1 (VDD), D2.1 (VDD), D3.1 (VDD), D4.1 (VDD), D5.1 (VDD), D6.1 (VDD), D7.1 (VDD), D8.1 (VDD), D9.1 (VDD), D10.1 (VDD), D11.1 (VDD), D12.1 (VDD), D13.1 (VDD), D14.1 (VDD), D15.1 (VDD), D16.1 (VDD), U1.5 (VCC), U2.5 (VCC), U3.1 (OUT)
SPI1_MISO: U7.14 (PA6), U8.2 (DO/IO_{1})
SPI1_MOSI: U7.15 (PA7), U8.5 (DI/IO_{0})
SPI1_SCK: U7.13 (PA5), U8.6 (CLK)
SWCLK: J2.4 (SWCLK), U7.37 (PA14)
SWDIO: J2.2 (SWDIO), U7.36 (PA13)
SWO: J2.6 (SWO), U7.41 (PB3)
VBUS: C3.2, C8.1, C10.1, R3.2, R4.1, U3.6 (IN), U4.3 (VI), U5.4 (-), U5.5 (V+)
kA: R7.1, SW1.2, U7.27 (PB14), U9.2
kB: R8.1, SW2.2, U7.29 (PC6), U11.2
kC: R11.1, SW3.2, U7.47 (PB9), U13.2
kD: R12.1, SW4.2, U7.45 (PB7), U16.2
kE: SW5.2, U7.26 (PB13)
kF: SW6.2, U7.28 (PB15)
kG: SW7.2, U7.2 (PC13)
kH: SW8.2, U7.4 (PC15)
kI: SW9.2, U7.25 (PB12)
kJ: SW10.2, U7.17 (PB0)
kK: SW11.2, U7.10 (PA2)
kL: SW12.2, U7.8 (PA0)
kM: SW13.2, U7.24 (PB11)
kN: SW14.2, U7.12 (PA4)
kO: SW15.2, U7.11 (PA3)
kP: SW16.2, U7.9 (PA1)
nRST: C27.1, J2.3 (~RESET), R13.1, SW19.1, SW19.2, U7.7 (PG10)
~RGB_EN: U3.4 (~EN), U7.40 (PC11)
~RGB_FAULT: R1.1, U3.3 (~FAULT), U7.39 (PC10)

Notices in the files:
boards/valletw__esp-atx-power__esp-atx-power/unrouted.kicad_pcb:
MIT License
